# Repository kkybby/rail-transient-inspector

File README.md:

# Hardware and engineering projects

Board-level interface design, motion-state logic and supporting bench-analysis tools.

[中文介绍](README.zh-CN.md)

## Featured hardware: LIMIT4

A four-channel limit-switch interface for small dual-actuator projects. The work includes an editable two-layer PCB, input-conditioning circuits, independent motion-state code and reproducible design checks.

**Stage:** unbuilt engineering prototype. The software has been tested and cross-compiled; the supplied Pico 2 program keeps motor outputs disabled. No physical motor performance is claimed.

**[Explore the hardware project](https://github.com/kkybby/rail-transient-inspector/tree/hardware/dual-actuator-controller-r0)** | [View the schematic](https://github.com/kkybby/rail-transient-inspector/blob/hardware/dual-actuator-controller-r0/build/limit4-schematic.pdf) | [中文作品页](https://github.com/kkybby/rail-transient-inspector/blob/hardware/dual-actuator-controller-r0/README.zh-CN.md)

The new interface extends the published OpenDualMotorDriver platform. The original motor-power motherboard is attributed to its author and is not represented as a new design. AI assistance was used for the extension and software; the project page separates reused work, new contributions and pending validation.

## Supporting tool: Rail Transient Inspector

Local oscilloscope CSV analysis for voltage dips and trigger timing. This software prototype includes explicit units, event filtering and HTML/JSON reports. Demonstration data is synthetic; real-instrument validation is pending.

[Software documentation](SOFTWARE.md) | [中文工具说明](SOFTWARE.zh-CN.md) | [Offline application file](standalone.html)

The repository retains its original name and software code on `main`. The hardware project is on the linked hardware branch. These links lead to project documentation and source, not a separately deployed website.

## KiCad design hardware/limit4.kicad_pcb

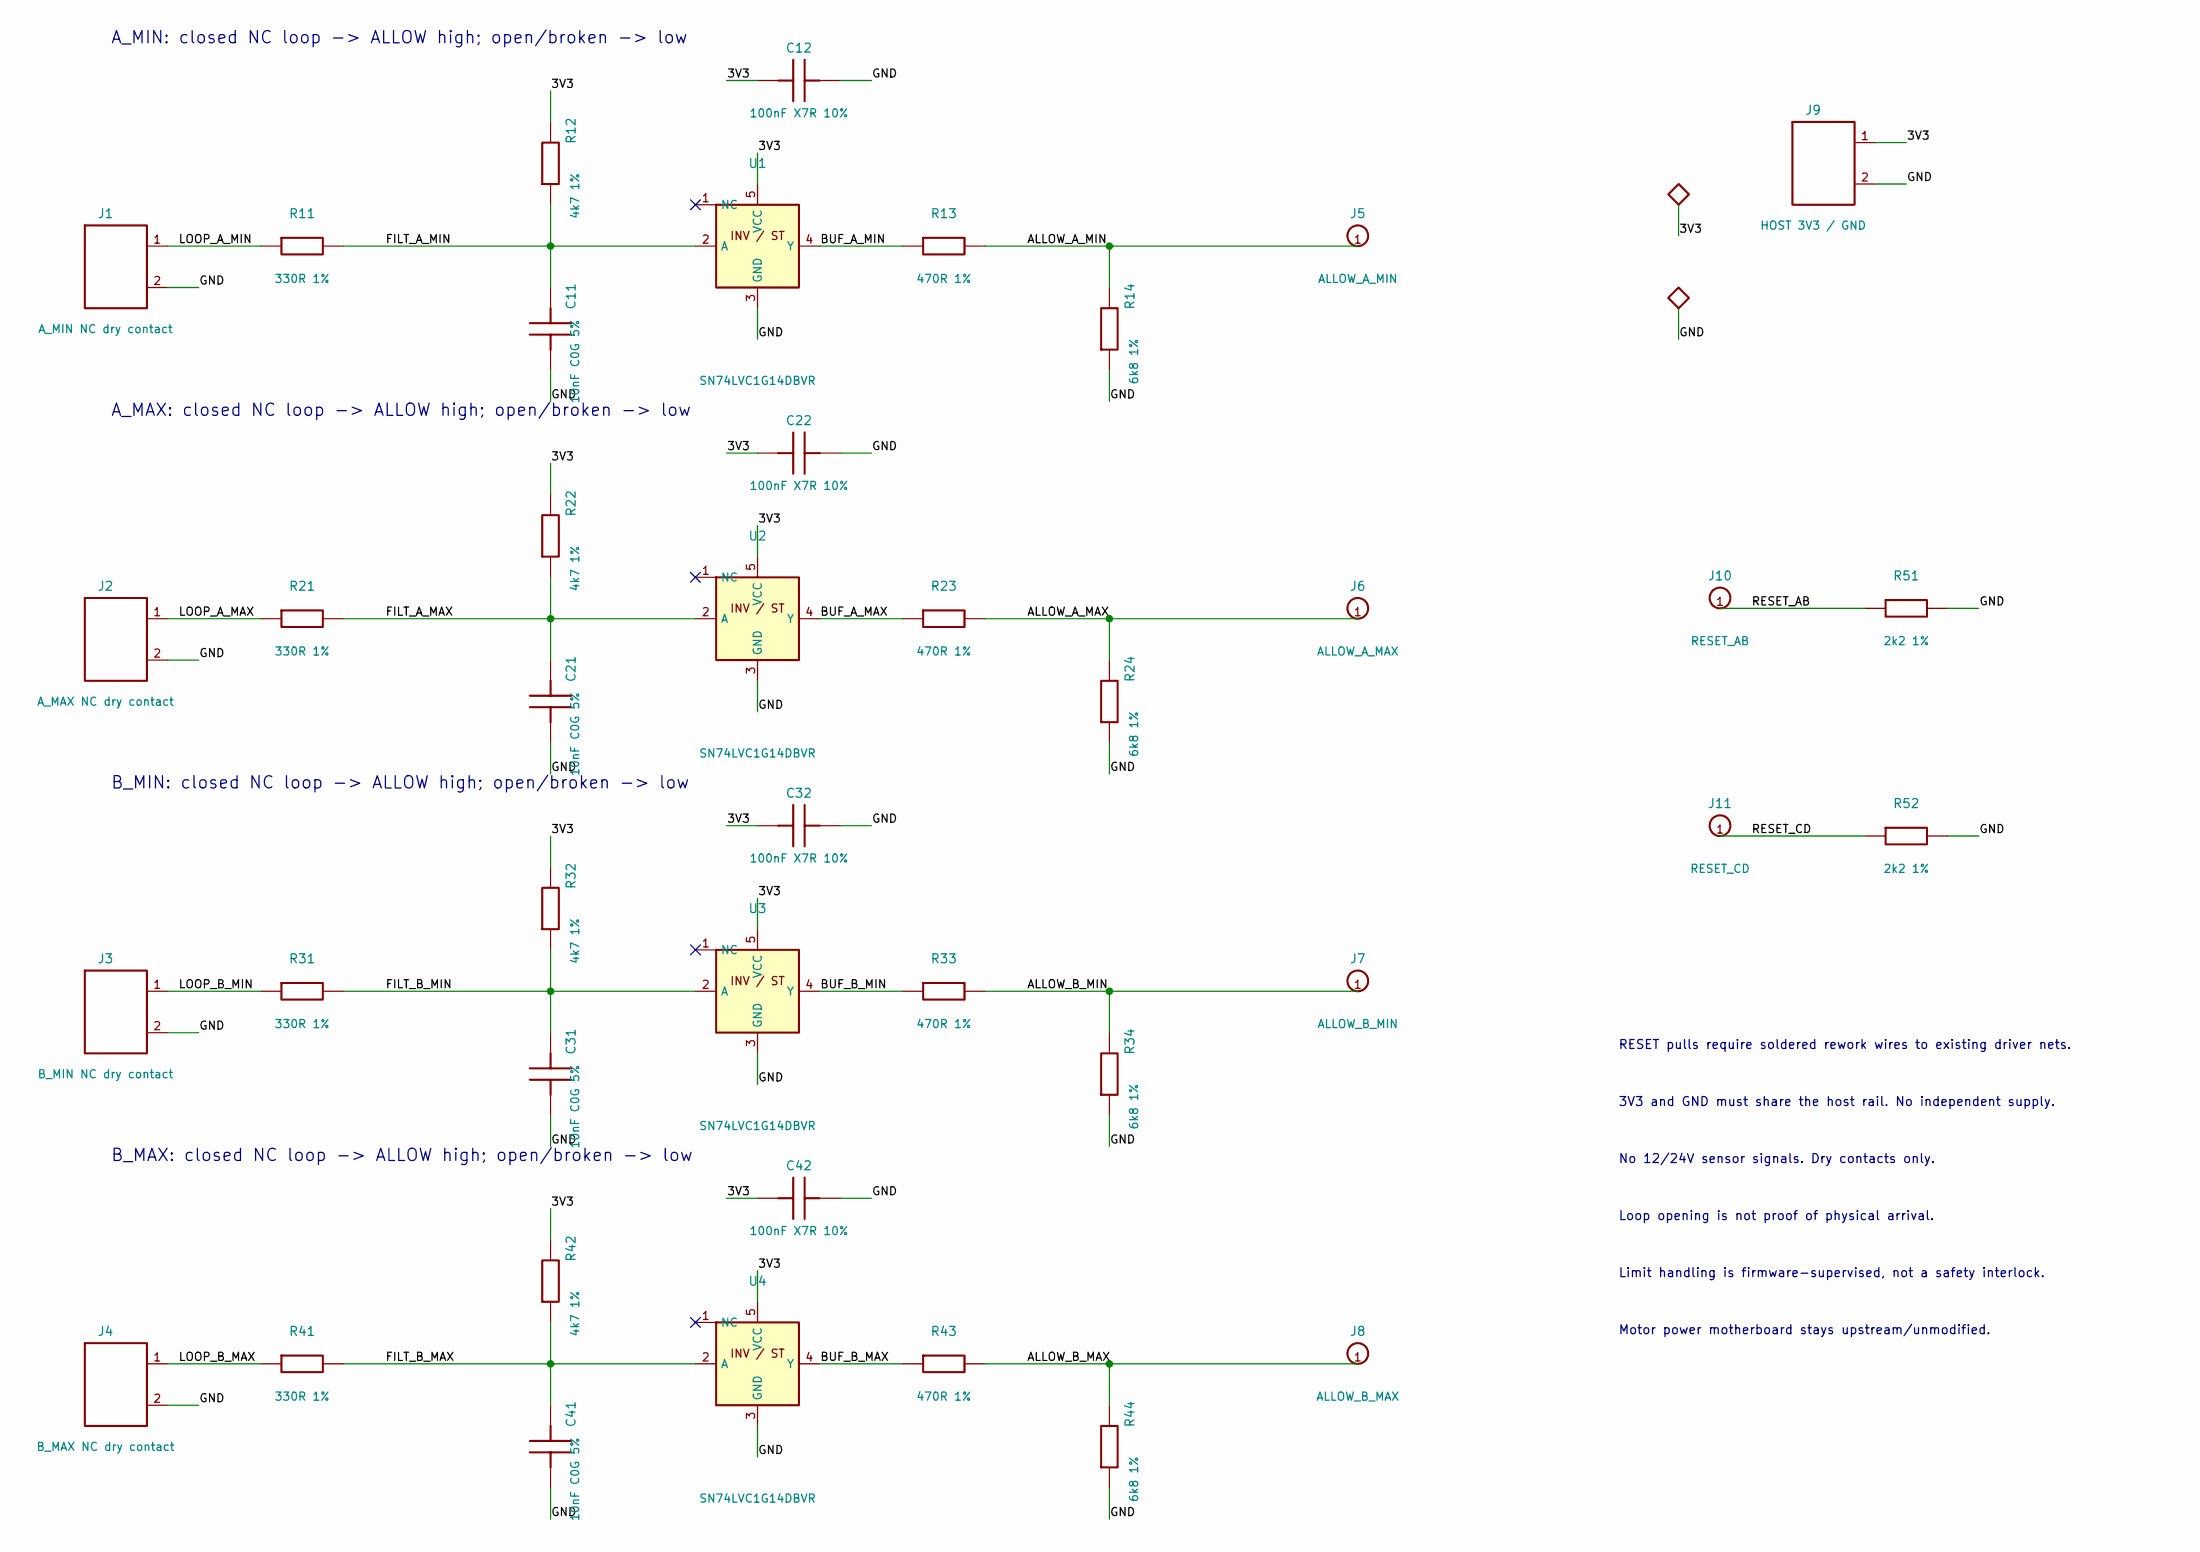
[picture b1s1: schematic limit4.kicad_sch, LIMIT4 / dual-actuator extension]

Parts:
C11, C21, C31, C41: 10nF C0G 5%; 0805
C12, C22, C32, C42: 100nF X7R 10%; 0805
J1: A_MIN NC dry contact; J2
J2: A_MAX NC dry contact; J2
J3: B_MIN NC dry contact; J2
J4: B_MAX NC dry contact; J2
J5: ALLOW_A_MIN; J1
J6: ALLOW_A_MAX; J1
J7: ALLOW_B_MIN; J1
J8: ALLOW_B_MAX; J1
J9: HOST 3V3 / GND; J2
J10: RESET_AB; J1
J11: RESET_CD; J1
R11, R21, R31, R41: 330R 1%; 0805
R12, R22, R32, R42: 4k7 1%; 0805
R13, R23, R33, R43: 470R 1%; 0805
R14, R24, R34, R44: 6k8 1%; 0805
R51, R52: 2k2 1%; 0805
U1, U2, U3, U4: SN74LVC1G14DBVR; DBV5

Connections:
3V3: C12.1, C22.1, C32.1, C42.1, J9.1, R12.2, R22.2, R32.2, R42.2, U1.5 (VCC), U2.5 (VCC), U3.5 (VCC), U4.5 (VCC)
ALLOW_A_MAX: J6.1, R23.2, R24.2
ALLOW_A_MIN: J5.1, R13.2, R14.2
ALLOW_B_MAX: J8.1, R43.2, R44.2
ALLOW_B_MIN: J7.1, R33.2, R34.2
BUF_A_MAX: R23.1, U2.4 (Y)
BUF_A_MIN: R13.1, U1.4 (Y)
BUF_B_MAX: R43.1, U4.4 (Y)
BUF_B_MIN: R33.1, U3.4 (Y)
FILT_A_MAX: C21.2, R21.2, R22.1, U2.2 (A)
FILT_A_MIN: C11.2, R11.2, R12.1, U1.2 (A)
FILT_B_MAX: C41.2, R41.2, R42.1, U4.2 (A)
FILT_B_MIN: C31.2, R31.2, R32.1, U3.2 (A)
GND: C11.1, C12.2, C21.1, C22.2, C31.1, C32.2, C41.1, C42.2, J1.2, J2.2, J3.2, J4.2, J9.2, R14.1, R24.1, R34.1, R44.1, R51.2, R52.2, U1.3 (GND), U2.3 (GND), U3.3 (GND), U4.3 (GND)
LOOP_A_MAX: J2.1, R21.1
LOOP_A_MIN: J1.1, R11.1
LOOP_B_MAX: J4.1, R41.1
LOOP_B_MIN: J3.1, R31.1
RESET_AB: J10.1, R51.1
RESET_CD: J11.1, R52.1

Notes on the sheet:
A_MIN: closed NC loop -> ALLOW high; open/broken -> low
A_MAX: closed NC loop -> ALLOW high; open/broken -> low
B_MIN: closed NC loop -> ALLOW high; open/broken -> low
B_MAX: closed NC loop -> ALLOW high; open/broken -> low
RESET pulls require soldered rework wires to existing driver nets.
3V3 and GND must share the host rail. No independent supply.
No 12/24V sensor signals. Dry contacts only.
Loop opening is not proof of physical arrival.
Limit handling is firmware-supervised, not a safety interlock.
Motor power motherboard stays upstream/unmodified.

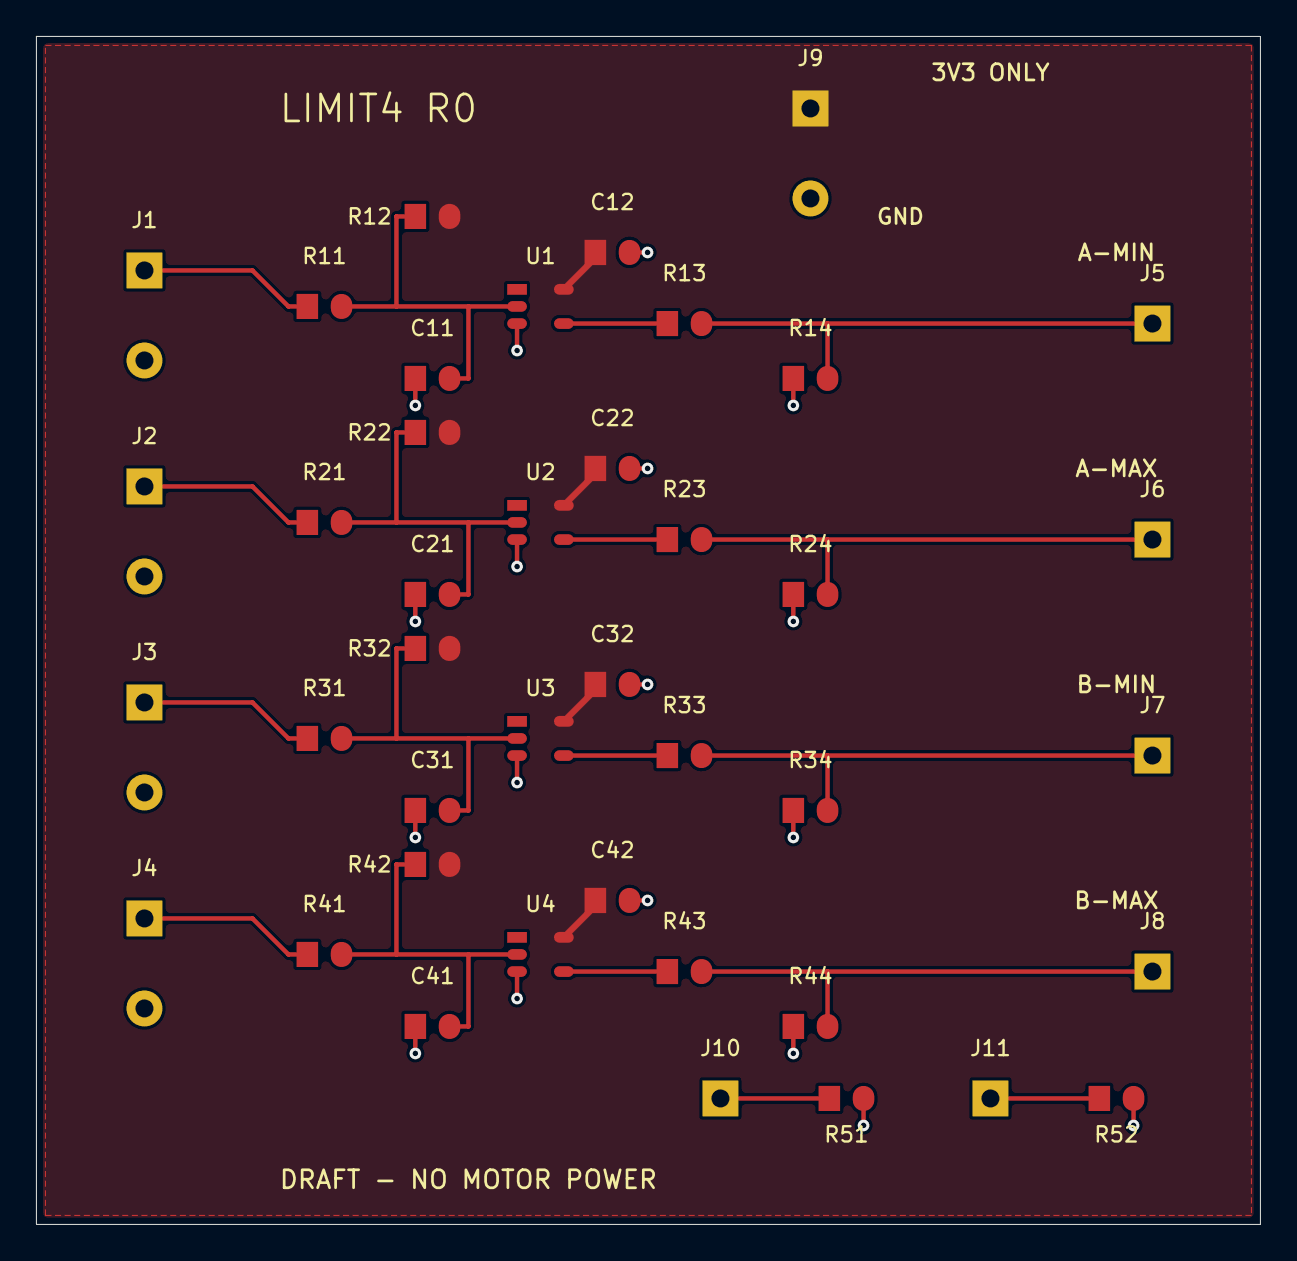
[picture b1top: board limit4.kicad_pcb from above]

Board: 2 copper layers, 68.0 x 66.0 mm, 41 parts (0 on the bottom side), 20 nets.

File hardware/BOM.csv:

Reference,Value,Candidate_MPN,Footprint,Qualification
J1,A_MIN NC dry contact,,1mm solder-wire holes,Wire termination only; no mating connector claimed
R11,330R 1%,SPEC_ONLY_MPN_PENDING,0805,Exact TI IC checked; passive sourcing/assembly approval pending
R12,4k7 1%,SPEC_ONLY_MPN_PENDING,0805,Exact TI IC checked; passive sourcing/assembly approval pending
C11,10nF C0G 5%,SPEC_ONLY_MPN_PENDING,0805,Exact TI IC checked; passive sourcing/assembly approval pending
U1,SN74LVC1G14DBVR,SN74LVC1G14DBVR,DBV-5,Exact TI IC checked; passive sourcing/assembly approval pending
C12,100nF X7R 10%,SPEC_ONLY_MPN_PENDING,0805,Exact TI IC checked; passive sourcing/assembly approval pending
R13,470R 1%,SPEC_ONLY_MPN_PENDING,0805,Exact TI IC checked; passive sourcing/assembly approval pending
R14,6k8 1%,SPEC_ONLY_MPN_PENDING,0805,Exact TI IC checked; passive sourcing/assembly approval pending
J5,ALLOW_A_MIN,,1mm solder-wire holes,Wire termination only; no mating connector claimed
J2,A_MAX NC dry contact,,1mm solder-wire holes,Wire termination only; no mating connector claimed
R21,330R 1%,SPEC_ONLY_MPN_PENDING,0805,Exact TI IC checked; passive sourcing/assembly approval pending
R22,4k7 1%,SPEC_ONLY_MPN_PENDING,0805,Exact TI IC checked; passive sourcing/assembly approval pending
C21,10nF C0G 5%,SPEC_ONLY_MPN_PENDING,0805,Exact TI IC checked; passive sourcing/assembly approval pending
U2,SN74LVC1G14DBVR,SN74LVC1G14DBVR,DBV-5,Exact TI IC checked; passive sourcing/assembly approval pending
C22,100nF X7R 10%,SPEC_ONLY_MPN_PENDING,0805,Exact TI IC checked; passive sourcing/assembly approval pending
R23,470R 1%,SPEC_ONLY_MPN_PENDING,0805,Exact TI IC checked; passive sourcing/assembly approval pending
R24,6k8 1%,SPEC_ONLY_MPN_PENDING,0805,Exact TI IC checked; passive sourcing/assembly approval pending
J6,ALLOW_A_MAX,,1mm solder-wire holes,Wire termination only; no mating connector claimed
J3,B_MIN NC dry contact,,1mm solder-wire holes,Wire termination only; no mating connector claimed
R31,330R 1%,SPEC_ONLY_MPN_PENDING,0805,Exact TI IC checked; passive sourcing/assembly approval pending
R32,4k7 1%,SPEC_ONLY_MPN_PENDING,0805,Exact TI IC checked; passive sourcing/assembly approval pending
C31,10nF C0G 5%,SPEC_ONLY_MPN_PENDING,0805,Exact TI IC checked; passive sourcing/assembly approval pending
U3,SN74LVC1G14DBVR,SN74LVC1G14DBVR,DBV-5,Exact TI IC checked; passive sourcing/assembly approval pending
C32,100nF X7R 10%,SPEC_ONLY_MPN_PENDING,0805,Exact TI IC checked; passive sourcing/assembly approval pending
R33,470R 1%,SPEC_ONLY_MPN_PENDING,0805,Exact TI IC checked; passive sourcing/assembly approval pending
R34,6k8 1%,SPEC_ONLY_MPN_PENDING,0805,Exact TI IC checked; passive sourcing/assembly approval pending
J7,ALLOW_B_MIN,,1mm solder-wire holes,Wire termination only; no mating connector claimed
J4,B_MAX NC dry contact,,1mm solder-wire holes,Wire termination only; no mating connector claimed
R41,330R 1%,SPEC_ONLY_MPN_PENDING,0805,Exact TI IC checked; passive sourcing/assembly approval pending
R42,4k7 1%,SPEC_ONLY_MPN_PENDING,0805,Exact TI IC checked; passive sourcing/assembly approval pending
C41,10nF C0G 5%,SPEC_ONLY_MPN_PENDING,0805,Exact TI IC checked; passive sourcing/assembly approval pending
U4,SN74LVC1G14DBVR,SN74LVC1G14DBVR,DBV-5,Exact TI IC checked; passive sourcing/assembly approval pending
C42,100nF X7R 10%,SPEC_ONLY_MPN_PENDING,0805,Exact TI IC checked; passive sourcing/assembly approval pending
R43,470R 1%,SPEC_ONLY_MPN_PENDING,0805,Exact TI IC checked; passive sourcing/assembly approval pending
R44,6k8 1%,SPEC_ONLY_MPN_PENDING,0805,Exact TI IC checked; passive sourcing/assembly approval pending
J8,ALLOW_B_MAX,,1mm solder-wire holes,Wire termination only; no mating connector claimed
J9,HOST 3V3 / GND,,1mm solder-wire holes,Wire termination only; no mating connector claimed
J10,RESET_AB,,1mm solder-wire holes,Wire termination only; no mating connector claimed
R51,2k2 1%,SPEC_ONLY_MPN_PENDING,0805,Exact TI IC checked; passive sourcing/assembly approval pending
J11,RESET_CD,,1mm solder-wire holes,Wire termination only; no mating connector claimed
R52,2k2 1%,SPEC_ONLY_MPN_PENDING,0805,Exact TI IC checked; passive sourcing/assembly approval pending
